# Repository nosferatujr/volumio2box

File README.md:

PRinted box for RPi2 | HiFiBerry DAC+ | Proper poweroff (GPIO)  

You can find openscad files for the box on the BOX folder  
The Eagle PCB files on PCB folder  
The Pic microcontroller files, including the HEX on PowerController_PIC folder  
The off_button.py on the python folder. This file contain instruictions to be copied on the RPi, install dependencies, and run on the startup.  

    TO2:
    include photos for the conexion of all pcb inside the box
    put all this in a volumio plugin (pin configurable)

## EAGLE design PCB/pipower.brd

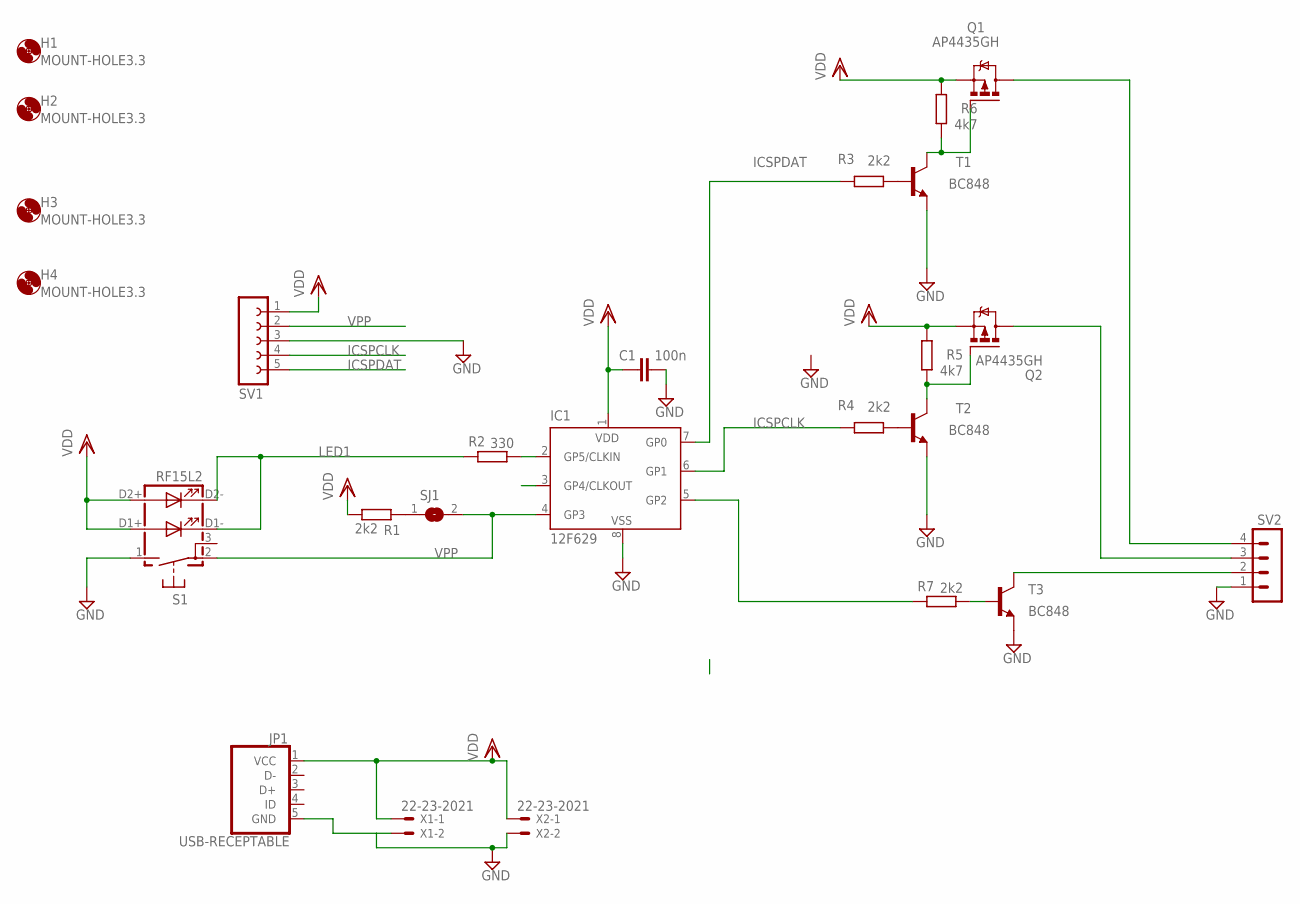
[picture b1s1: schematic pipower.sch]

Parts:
C1: 100n; C0805
H1, H2, H3, H4: MOUNT-HOLE3.3; 3,3
IC1: 12F629; SO-08; MPN PIC12F629-I/SN
JP1: USB-RECEPTABLE; FCI-10103594-0001LF
Q1, Q2: AP4435GH; D-PAK_TO252AA
R1, R3, R4, R7: 2k2; R0805
R2: 330; R0805
R5, R6: 4k7; R0805
S1: RF15L2
SJ1: SJ
SV1: FE05-1
SV2: MA04-1
T1, T2, T3: BC848; SOT23
X1, X2: 22-23-2021

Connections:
GND: C1.2, IC1.8 (VSS), JP1.5 (GND), S1.1 (S), SV1.3, SV2.1, T1.2 (E), T2.2 (E), T3.2 (E), X1.2, X2.2
ICSPCLK: IC1.6 (GP1), R4.2, SV1.4
ICSPDAT: IC1.7 (GP0), R3.2, SV1.5
LED1: R2.2, S1.D1- (C1), S1.D2- (C2)
unnamed: IC1.5 (GP2), R7.2
unnamed: Q1.4 (D), SV2.4
unnamed: Q2.1 (G), R5.1, T2.3 (C)
unnamed: R3.1, T1.1 (B)
unnamed: R1.2, SJ1.1
unnamed: R4.1, T2.1 (B)
unnamed: Q2.4 (D), SV2.3
unnamed: Q1.1 (G), R6.1, T1.3 (C)
unnamed: IC1.2 (GP5/CLKIN), R2.1
unnamed: SV2.2, T3.3 (C)
unnamed: R7.1, T3.1 (B)
VDD: C1.1, IC1.1 (VDD), JP1.1 (VCC), Q1.3 (S), Q2.3 (S), R1.1, R5.2, R6.2, S1.D1+ (A1), S1.D2+ (A2), SV1.1, X1.1, X2.1
VPP: IC1.4 (GP3), S1.2, SJ1.2, SV1.2

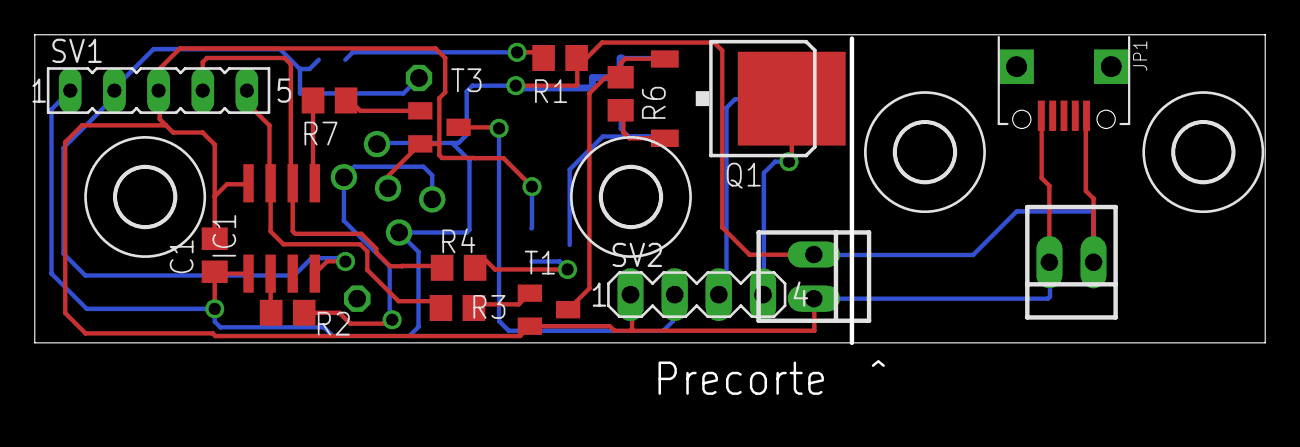
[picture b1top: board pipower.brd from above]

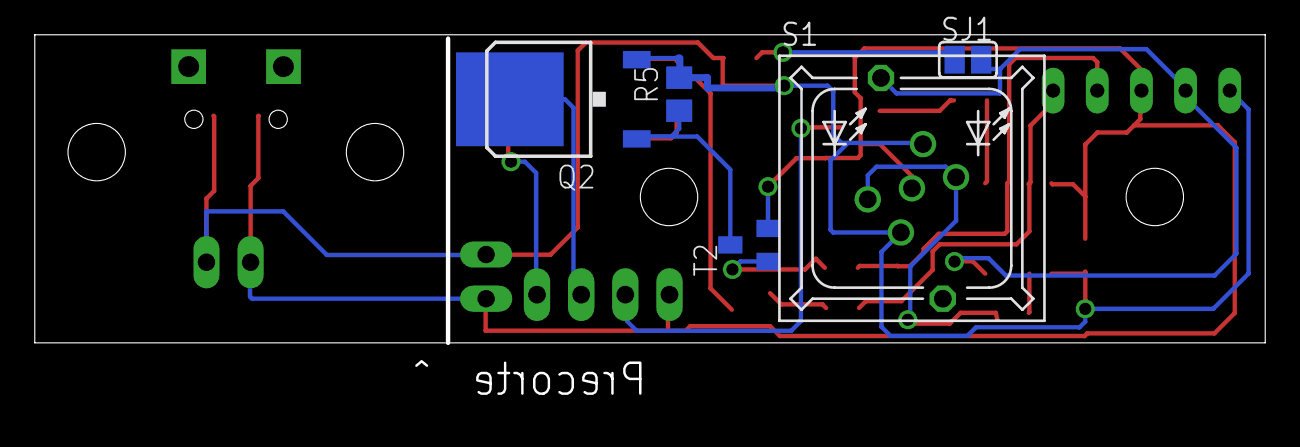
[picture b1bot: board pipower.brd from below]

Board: 2 copper layers, 70.8 x 17.7 mm, 25 parts (5 on the bottom side), 17 nets.

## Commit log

2016-06-30 the openscad files
2016-06-30 added python script
2016-06-30 added Eagle Pcb files
2016-06-30 PiC files
2016-06-30 renamed
2016-06-30 updated nl
2016-06-30 add to2
